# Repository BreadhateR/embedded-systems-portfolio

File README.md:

# Embedded Systems & PCB Design Portfolio

Hardware designs and experimental work from my master's thesis on the power supply of **[SiSmaK – Sensor-integrated machine element](https://www.spp2305.de/sismak/)** at TU Darmstadt. SiSmaK is a sensor-integrated M20 bolt that measures multiaxial mechanical loads using strain gauges and transmits the readings wirelessly. The thesis investigated photovoltaic harvesting, externally driven ultrasonic power transfer, and NFC power transfer as alternative supplies for the existing sensor electronics.

My work covered power-supply concepts, component selection, schematic and PCB design, analog measurement circuits, firmware adaptations, system integration, and experimental characterization. The main challenges were the approximately **13 mm PCB diameter**, limited storage capacity, and MCU startup and measurement bursts that exceed the available harvesting power. Each project README explains its circuit, design decisions, and validation scope alongside the KiCad files and existing hardware PDF.

## Projects

| Project | Focus | Documentation |
| --- | --- | --- |
| **[MCU Board](Kicad_Files/MCU_Board/)** | Separate Nordic MCU development-board design with RF, SWD and GPIO interfaces | [README](Kicad_Files/MCU_Board/README.md) · [Hardware design](Kicad_Files/MCU_Board/Hardware_Design.pdf) |
| **[Solar Harvester — Battery](Kicad_Files/Harvesting_Solar_Akku/)** | AEM10300 photovoltaic supply using the existing SiSmaK rechargeable cell | [README](Kicad_Files/Harvesting_Solar_Akku/README.md) · [Hardware design](Kicad_Files/Harvesting_Solar_Akku/Hardware_Design.pdf) |
| **[Solar Harvester — Capacitor](Kicad_Files/Harvester_Solar_Kondensator/)** | Photovoltaic supply with 150 µF storage and a storage-controlled output gate | [README](Kicad_Files/Harvester_Solar_Kondensator/README.md) · [Hardware design](Kicad_Files/Harvester_Solar_Kondensator/Hardware_Design.pdf) |
| **[Piezo Harvester — Battery](Kicad_Files/Harvester_Piezo_Akku/)** | Ultrasonic receiver supply with Greinacher rectification and AEM30300 load adjustment | [README](Kicad_Files/Harvester_Piezo_Akku/README.md) · [Hardware design](Kicad_Files/Harvester_Piezo_Akku/Hardware_Design.pdf) |
| **[Piezo Harvester — Capacitor](Kicad_Files/Harvester_Piezo_Kondensator/)** | Ultrasonic supply architecture with capacitor storage and phased measurement operation | [README](Kicad_Files/Harvester_Piezo_Kondensator/README.md) · [Hardware design](Kicad_Files/Harvester_Piezo_Kondensator/Hardware_Design.pdf) |
| **[Piezo Harvester with Measurements](Kicad_Files/Harvester_Piezo_WithMeasurements/)** | Compact rectifier-output voltage/current measurement design for frequency ranking | [README](Kicad_Files/Harvester_Piezo_WithMeasurements/README.md) · [Hardware design](Kicad_Files/Harvester_Piezo_WithMeasurements/Hardware_Design.pdf) |
| **[Piezo Harvesting & Resonance Evaluation Board](Kicad_Files/Harvester_Piezo_WithMeasurements__DevBoard/)** | Configurable harvesting and measurement platform with XIAO nRF54L15 and SiSmaK interfaces | [README](Kicad_Files/Harvester_Piezo_WithMeasurements__DevBoard/README.md) · [Hardware design](Kicad_Files/Harvester_Piezo_WithMeasurements__DevBoard/Hardware_Design.pdf) |
| **[NFC Harvester](Kicad_Files/NFC_Harvester/)** | NTAG 5 Link receiver with antenna tuning and reverse-current blocking | [README](Kicad_Files/NFC_Harvester/README.md) · [Hardware design](Kicad_Files/NFC_Harvester/Hardware_Design.pdf) |

## Repository Structure

```text
Kicad_Files/
├── MCU_Board/
├── Harvesting_Solar_Akku/
├── Harvester_Solar_Kondensator/
├── Harvester_Piezo_Akku/
├── Harvester_Piezo_Kondensator/
├── Harvester_Piezo_WithMeasurements/
├── Harvester_Piezo_WithMeasurements__DevBoard/
├── NFC_Harvester/
└── Libraries/
    ├── 3D/
    ├── Footprints/
    └── Symbols/
```

Project directories generally include:

- `*.kicad_pro`, `*.kicad_sch`, `*.kicad_pcb` — editable KiCad project, schematic, and PCB layout
- `README.md` — project-specific description
- `Hardware_Design.pdf` — exported hardware documentation
- `images/` — board renders or layout images
- `bom/` — bill-of-materials exports where available, including interactive BOMs

Shared custom symbols, footprints, and 3D models are located in [`Kicad_Files/Libraries/`](Kicad_Files/Libraries/).

## Viewing the Designs

Open a project's `.kicad_pro` file in **KiCad** to inspect its schematic and PCB layout. For a quick overview without KiCad, use the project's README, PDF documentation, and available interactive BOM (`bom/ibom.html`).

## Project Context

The existing SiSmaK sensor electronics, flexible PCB, and overall bolt concept formed the integration baseline. The harvesting modules and associated firmware/measurement work documented here extend that system; they do not represent development of the complete SiSmaK platform.

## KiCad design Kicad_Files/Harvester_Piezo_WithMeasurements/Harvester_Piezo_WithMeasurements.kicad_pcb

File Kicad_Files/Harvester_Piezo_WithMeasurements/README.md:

# SiSmaK – Piezoelectric Resonance Measurement Board

Compact harvesting and measurement PCB developed for the [SiSmaK research project](https://www.spp2305.de/sismak/) at TU Darmstadt. It investigates how frequency-search electronics can fit within the approximately 13 mm installation envelope of the sensor-integrated M20 bolt.

The board combines AEM30300 harvesting with switchable measurement paths at the **DC output of the Greinacher rectifier**. Measuring open-circuit voltage and approximate short-circuit current at different excitation frequencies supports ranking of useful ultrasonic operating points without a full load sweep at every frequency.

Development focused on the analog signal paths, MCU-controlled measurement states, and two-sided PCB integration. An FPC interface routes supply, control, and measurement signals to the existing SiSmaK electronics; a separate development board provides access for commissioning and experiments.

## PCB Design

<table>
  <tr>
    <th align="center">Front Side</th>
    <th align="center">Back Side</th>
  </tr>
  <tr>
    <td width="50%" align="center"></td>
    <td width="50%" align="center"></td>
  </tr>
</table>

## Hardware Overview

- **Energy Harvesting IC:** e-peas AEM30300 for piezoelectric energy harvesting and power management.
- **Piezoelectric Input:** External piezoelectric transducer connected through an MHF4 connector.
- **Rectification:** Greinacher voltage doubler using Schottky diodes for converting the piezoelectric AC signal into DC voltage.
- **Current Measurement:** INA190 current-sense amplifier with a 30 Ω shunt; the thesis uses 200 V/V gain.
- **Voltage Measurement:** 6.8 MΩ / 3.3 MΩ divider, approximately 1:3 reduction, with an ADC charge-buffer capacitor.
- **Measurement Control:** MOSFET-based switching circuit for controlling the measurement conditions.
- **System Interface:** FPC connection to the existing SiSmaK electronics, carrying power, measurement signals and control connections.
- **Form Factor:** Compact circular PCB designed for integration into the space-constrained SiSmaK assembly.

## Operating Principle

The circuit separates energy collection from voltage/current characterization so the changing operating state of the harvesting IC has less influence on comparisons between excitation frequencies.

### Piezoelectric Energy Harvesting

The alternating voltage generated by the piezoelectric transducer is rectified using a Greinacher voltage doubler consisting of Schottky diodes and capacitors.

The resulting DC voltage is supplied to the AEM30300 energy harvesting IC, which manages the harvested energy and provides an interface for the connected system.

### Resonance Characterization

The nRF54L15's internal ADC acquires the rectifier-output measurements, avoiding an additional external ADC on the compact module.

- **Open-Circuit Voltage (Voc):** Storage charging is disabled to reduce harvester loading. The AEM30300 remains connected; the thesis found no relevant measurement influence after its supply capacitors had charged.
- **Short-Circuit Current (Isc):** A MOSFET switches the rectifier output through the low-resistance shunt path, and the INA190 amplifies the shunt voltage for ADC acquisition.

The SiSmaK microcontroller controls the measurement circuitry through the FPC interface, switching between open-circuit voltage and short-circuit current measurements. The measured signals are transferred through the same interface for acquisition and processing.

The product **Voc × Isc** is a frequency-ranking criterion, not power delivered into a load: its two factors are measured in different states. The thesis found a close empirical relationship to maximum available power for the investigated configuration (§5.4.1). Divider/filter settling after switching limits measurement speed; amplifier output swing limits the current range.

## Hardware Design Files

The KiCad schematic and PCB design files are included in the project directory for further inspection.

[View Hardware Design Documentation (PDF)](Hardware_Design.pdf)

## Project Context

This PCB was developed as part of research and development activities associated with the [SiSmaK project](https://www.spp2305.de/sismak/) at the Institute of Production Management, Technology and Machine Tools (PTW), TU Darmstadt.

The compact layout establishes the spatial feasibility of the measurement circuit (§5.4.2). Commissioning, firmware integration into the existing SiSmaK project, and experimental frequency sweeps are reported with the development setup (§5.4.3);

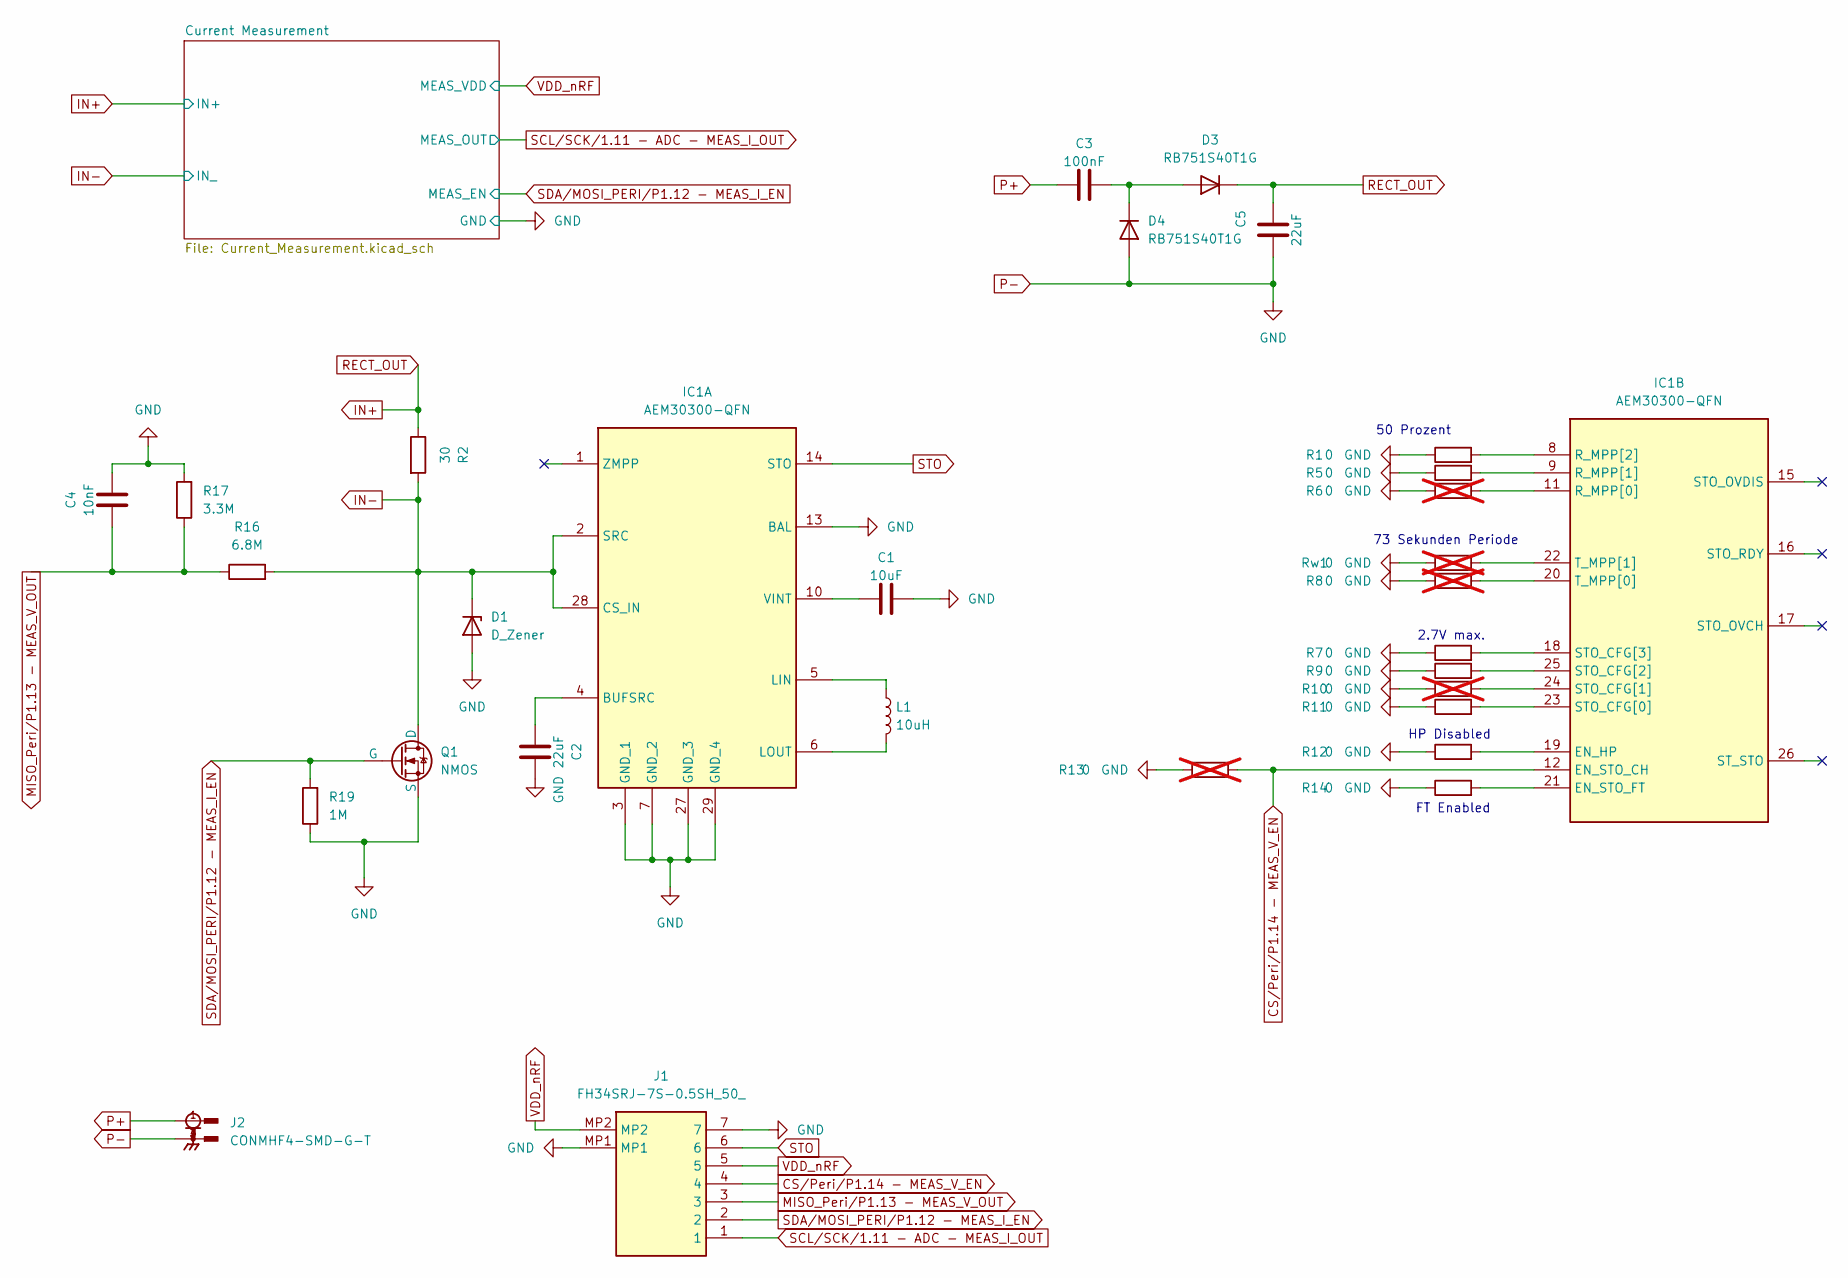
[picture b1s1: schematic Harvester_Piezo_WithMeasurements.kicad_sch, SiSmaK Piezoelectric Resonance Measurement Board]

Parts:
C1: 10uF; C_0402_1005Metric_Pad0.74x0.62mm_HandSolder; MPN GRM155R60J106ME15D
C2: 22uF; C_0603_1608Metric; MPN GRM188R61A226ME15D
C3: 100nF; 0704; MPN GRMJN65C1H104JE01J
C4: 10nF; C_0402_1005Metric_Pad0.74x0.62mm_HandSolder; MPN GRM1555CYA103GE01J
C5: 22uF; C_0603_1608Metric; MPN MLASL168BB5226MTNA01
D1: D_Zener; SODFL1608X70N; MPN MM5Z5V6T1G
D3, D4: RB751S40T1G; Diode_RB751S40T1G; MPN RB751S40T1G
IC1: AEM30300-QFN; AEM30300; Manufacturer_Part_Number AEM30300-QFN
J1: FH34SRJ-7S-0.5SH_50_; FH34SRJ7S05SH50; Manufacturer_Part_Number FH34SRJ-7S-0.5SH(50); Mouser Part Number 798-FH34SRJ7S05SH50
J2: CONMHF4-SMD-G-T; PARTREV A
L1: 10uH; DFE252010F-100M=P2; MPN DFE252010F-100M=P2
Q1: NMOS; SOT-523; MPN DMN2310UTQ-7
R1, R5, R7, R9, R11, R12, R14: 0; R_01005_0402Metric; MPN RC0201JR-130RL
R2: 30; R_0402_1005Metric_Pad0.72x0.64mm_HandSolder; MPN RT0402BRE0730RL
R6, R8, R10, R13: 0; R_01005_0402Metric; MPN RC0201JR-130RL; not fitted
R16: 6.8M; R_0402_1005Metric_Pad0.72x0.64mm_HandSolder; MPN RC0402FR-076M8L
R17: 3.3M; R_0402_1005Metric_Pad0.72x0.64mm_HandSolder; MPN CRCW04023M30FKEDC
R19: 1M; R_0402_1005Metric_Pad0.72x0.64mm_HandSolder; MPN RC0402FR-071MP
Rw1: 0; R_01005_0402Metric; MPN RC0201JR-130RL; not fitted

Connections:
CS/Peri/P1.14 - MEAS_V_EN: IC1.12 (EN_STO_CH), J1.4, R13.2
IN+: C5.2, D3.1 (K), R2.1; also elsewhere on the board
IN-: D1.1 (K), IC1.2 (SRC), IC1.28 (CS_IN), Q1.3 (D), R2.2, R16.2; also elsewhere on the board
MISO_Peri/P1.13 - MEAS_V_OUT: C4.2, J1.3, R16.1, R17.1
unnamed: C3.1, D3.2 (A), D4.1 (K)
unnamed: C2.2, IC1.4 (BUFSRC)
unnamed: IC1.5 (LIN), L1.1
unnamed: IC1.6 (LOUT), L1.2
unnamed: C1.2, IC1.10 (VINT)
unnamed: IC1.19 (EN_HP), R12.2
unnamed: IC1.21 (EN_STO_FT), R14.2
unnamed: IC1.11 (R_MPP[0]), R6.2
unnamed: IC1.9 (R_MPP[1]), R5.2
unnamed: IC1.8 (R_MPP[2]), R1.2
unnamed: IC1.23 (STO_CFG[0]), R11.2
unnamed: IC1.24 (STO_CFG[1]), R10.2
unnamed: IC1.25 (STO_CFG[2]), R9.2
unnamed: IC1.18 (STO_CFG[3]), R7.2
unnamed: IC1.20 (T_MPP[0]), R8.2
unnamed: IC1.22 (T_MPP[1]), Rw1.2
P+: C3.2, J2.1
P-: C1.1, C2.1, C4.1, C5.1, D1.2 (A), D4.2 (A), IC1.3 (GND_1), IC1.7 (GND_2), IC1.13 (BAL), IC1.27 (GND_3), IC1.29 (GND_4), J1.7, J1.MP1, J2.2, J2.3, J2.4, Q1.2 (S), R1.1, R5.1, R6.1, R7.1, R8.1, R9.1, R10.1, R11.1, R12.1, R13.1, R14.1, R17.2, R19.1, Rw1.1; also elsewhere on the board
SCL/SCK/1.11 - ADC - MEAS_I_OUT: J1.1; also elsewhere on the board
SDA/MOSI_PERI/P1.12 - MEAS_I_EN: J1.2, Q1.1 (G), R19.2; also elsewhere on the board
STO: IC1.14 (STO), J1.6
VDD_nRF: J1.5, J1.MP2; also elsewhere on the board

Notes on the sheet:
FT Enabled
50 Prozent
73 Sekunden Periode
HP Disabled
2.7V max.

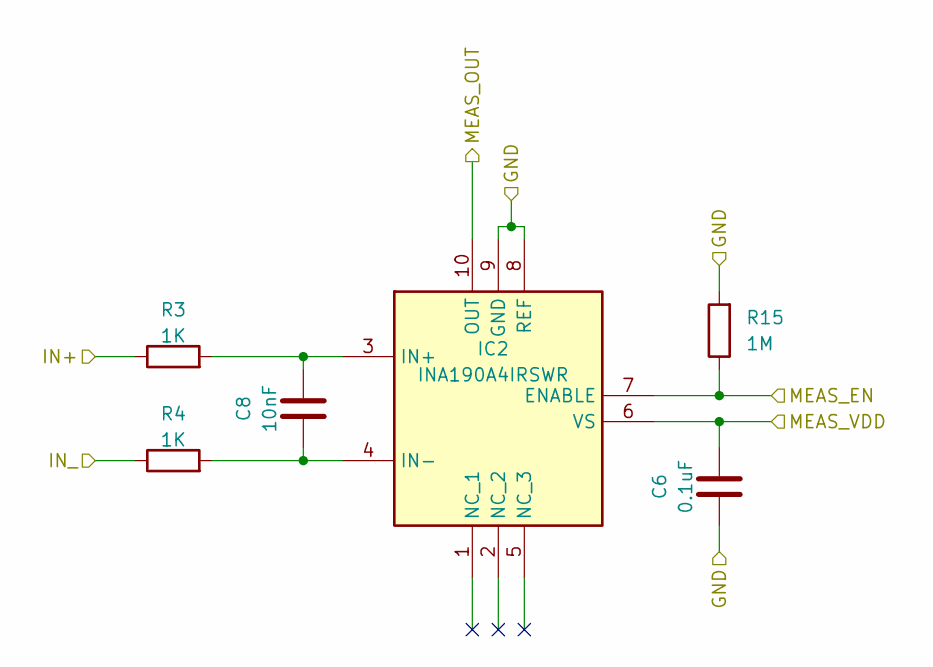
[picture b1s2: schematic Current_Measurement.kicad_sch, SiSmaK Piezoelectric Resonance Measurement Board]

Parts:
C6: 0.1uF; C_0402_1005Metric_Pad0.74x0.62mm_HandSolder; MPN CGA2B2X5R1C104M050BA
C8: 10nF; C_0402_1005Metric_Pad0.74x0.62mm_HandSolder; MPN GRM1555CYA103GE01J
IC2: INA190A4IRSWR; QFN40P140X180X55-10N; Manufacturer_Part_Number INA190A4IRSWR; Mouser Part Number 595-INA190A4IRSWR
R3, R4: 1K; R_0402_1005Metric_Pad0.72x0.64mm_HandSolder; MPN RNCF0402BTE1K00
R15: 1M; R_0402_1005Metric_Pad0.72x0.64mm_HandSolder; MPN RC0402FR-071MP

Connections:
IN+: R3.1; also elsewhere on the board
IN-: R4.1; also elsewhere on the board
unnamed: C8.1, IC2.3 (IN+), R3.2
unnamed: C8.2, IC2.4 (IN-), R4.2
P-: C6.2, IC2.8 (REF), IC2.9 (GND), R15.2; also elsewhere on the board
SCL/SCK/1.11 - ADC - MEAS_I_OUT: IC2.10 (OUT); also elsewhere on the board
SDA/MOSI_PERI/P1.12 - MEAS_I_EN: IC2.7 (ENABLE), R15.1; also elsewhere on the board
VDD_nRF: C6.1, IC2.6 (VS); also elsewhere on the board

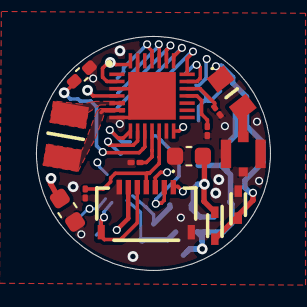
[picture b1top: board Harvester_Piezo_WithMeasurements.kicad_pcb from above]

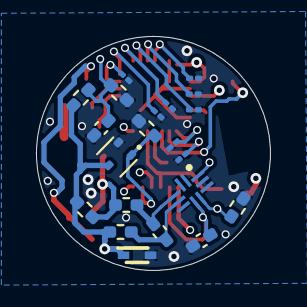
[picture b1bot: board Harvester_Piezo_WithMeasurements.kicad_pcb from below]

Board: 4 copper layers, 13.0 x 13.0 mm, 35 parts (21 on the bottom side), 28 nets.

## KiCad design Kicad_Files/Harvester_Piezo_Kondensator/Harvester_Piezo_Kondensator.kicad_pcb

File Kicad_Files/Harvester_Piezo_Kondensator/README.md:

# SiSmaK Piezoelectric Energy Harvesting Module – Capacitor

Capacitor-buffered ultrasonic supply design for the existing **[SiSmaK](https://www.spp2305.de/sismak/)** sensor-integrated M20 bolt. The circular PCB connects through an **FPC interface**, stores energy from an external piezoelectric receiver, and delays load connection until sufficient storage voltage is available.

Development combined rectification and storage circuitry, a controlled output path, compact PCB layout, and firmware adaptations that divide sensor acquisition into tasks separated by recharge pauses.

## Hardware Features

- **Energy Harvesting IC:** AEM30300 in the thesis architecture; supplied IC1 fields are inconsistent (see Project Status)
- **Energy Source:** External piezoelectric transducer
- **Piezoelectric Input:** External transducer connection via MHF4 connector
- **Rectification:** Greinacher voltage-doubler circuit using Schottky diodes
- **Energy Storage:** 150 µF nominal capacitor
- **Power Management:** Inductive DC-DC conversion and storage-voltage monitoring
- **Operating Concept:** Harvest–Store–Partial–Use, retaining RAM during sleep/recharge pauses
- **System Interface:** FPC connection to the existing SiSmaK electronics
- **Form Factor:** Compact circular PCB for space-constrained integration

### Piezoelectric Energy Harvesting

The piezoelectric receiver generates AC under externally driven ultrasonic excitation. A Greinacher voltage doubler rectifies the signal, and the harvesting stage transfers energy to the capacitor.

An ST_STO-controlled PMOS/NMOS output gate keeps the load disconnected during initial charging. Once enabled, the MCU boots and performs individual strain-gauge measurements, entering sleep between tasks while the capacitor recharges. Maintaining the MCU supply preserves RAM and avoids another energy-intensive boot.

### SiSmaK Integration

The module was designed as an add-on to the existing SiSmaK electronics rather than a standalone development board. The piezoelectric transducer connects through an MHF4 connector, while the FPC interface provides the electrical connection to the sensor-integrating bolt system. The FPC connector is visible on the back side of the PCB.

## PCB Design

The approximately 13 mm, four-layer PCB was designed in **KiCad 9**. Two-sided placement accommodates the rectifier, storage, and output-control circuitry; the FPC connector is on the reverse side.

### PCB View

<table>
  <tr>
    <th align="center">Front Side</th>
    <th align="center">Back Side</th>
  </tr>
  <tr>
    <td width="50%" align="center"></td>
    <td width="50%" align="center"></td>
  </tr>
</table>

## Hardware Design Documentation

The KiCad schematic and PCB design files are included for further inspection.

[View Hardware Design Documentation (PDF)](Hardware_Design.pdf)

## Design Files

| File | Description |
|---|---|
| `Harvester_Piezo_Kondensator.kicad_pro` | KiCad project |
| `Harvester_Piezo_Kondensator.kicad_sch` | Electrical schematic |
| `Harvester_Piezo_Kondensator.kicad_pcb` | PCB layout |
| `images/Harvester_Piezo_Kondensator.png` | Front-side 3D rendering |
| `images/Harvester_Piezo_Kondensator_hinten.png` | Back-side 3D rendering |
| `Hardware_Design.pdf` | Schematic and PCB documentation |

## Project Status

The thesis demonstrates phased operation with **150 µF storage** (§5.3.2): charging to about 3.3 V followed by successful MCU boot, with capacitor voltage falling to about 1.7 V. PPK2 recordings, GPIO timing markers, and oscilloscope measurements linked individual tasks to energy use and storage-voltage changes. Reported boot energy was about **0.58 mJ over 24.5 ms**; individual strain-gauge channels required about **0.30 mJ over 14 ms**.

---

**Author:** Alexander Richter  
**Institution:** TU Darmstadt  
**Related project:** [SiSmaK – Project Website](https://www.spp2305.de/sismak/)

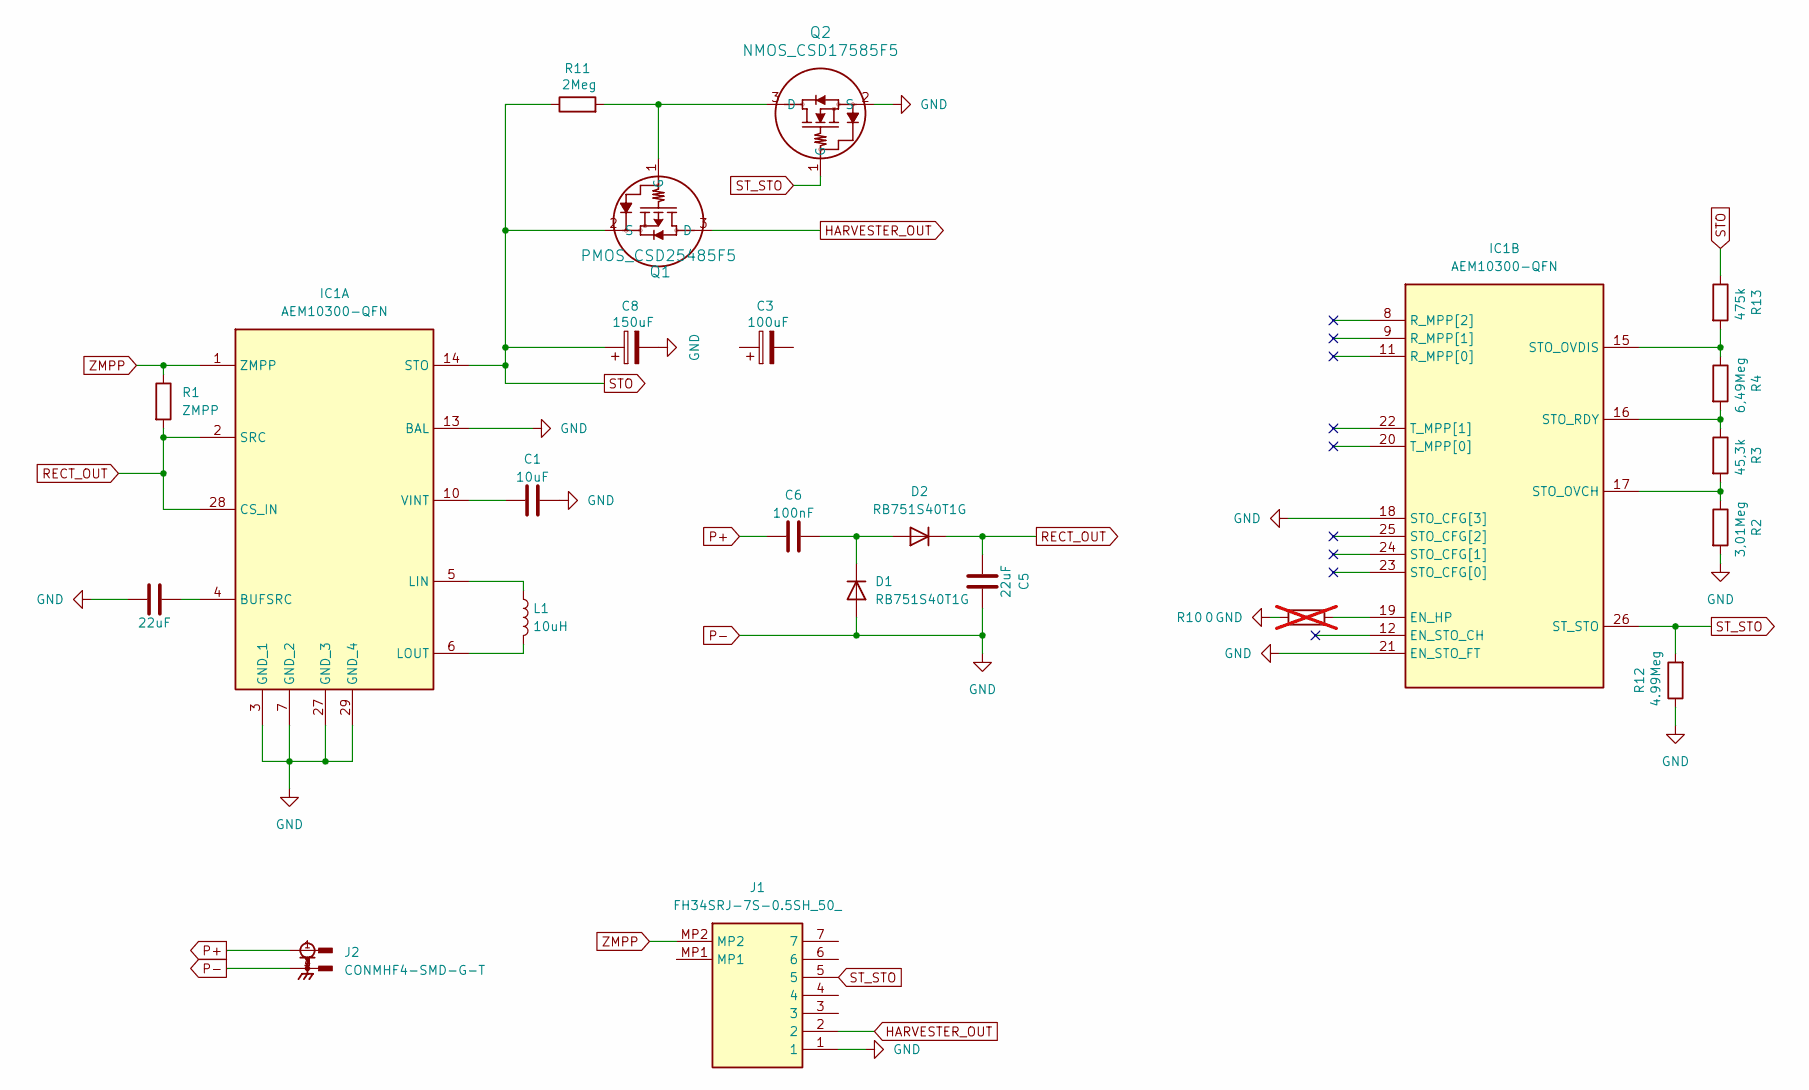
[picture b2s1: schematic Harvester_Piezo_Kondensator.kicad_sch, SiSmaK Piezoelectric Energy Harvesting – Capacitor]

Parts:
C1: 10uF; C_0402_1005Metric_Pad0.74x0.62mm_HandSolder; MPN GRM155R60J106ME15D
C2: 22uF; C_0603_1608Metric; MPN GRM188R61A226ME15D
C3: 100uF; TCTOBL1A107M8R-ZS1; MPN TCTOBL1A107M8R-ZS1
C5: 22uF; C_0603_1608Metric; MPN MLASL168BB5226MTNA01
C6: 100nF; 0704; MPN GRMJN65C1H104JE01J
C8: 150uF; T490B; MPN T490B157M010ATE500
D1, D2: RB751S40T1G; Diode_RB751S40T1G; MPN RB751S40T1G
IC1: AEM10300-QFN; AEM30300; Manufacturer_Part_Number AEM10300-QFN
J1: FH34SRJ-7S-0.5SH_50_; FH34SRJ7S05SH50; Manufacturer_Part_Number FH34SRJ-7S-0.5SH(50); Mouser Part Number 798-FH34SRJ7S05SH50
J2: CONMHF4-SMD-G-T; PARTREV A
L1: 10uH; DFE252010F-100M=P2; MPN DFE252010F-100M=P2
Q1: PMOS_CSD25485F5; MPN CSD25485F5
Q2: NMOS_CSD17585F5; MPN CSD17585F5
R1: ZMPP; R_0402_1005Metric_Pad0.72x0.64mm_HandSolder
R2: 3,01Meg; R_0402_1005Metric_Pad0.72x0.64mm_HandSolder; MPN CRCW04023M01FKED
R3: 45,3k; R_0402_1005Metric_Pad0.72x0.64mm_HandSolder; MPN 560112110243
R4: 6,49Meg; R_0402_1005Metric_Pad0.72x0.64mm_HandSolder; MPN RC0402FR-076M49L
R10: 0; C_0201_0603Metric_Pad0.64x0.40mm_HandSolder; not fitted
R11: 2Meg; R_0402_1005Metric_Pad0.72x0.64mm_HandSolder; MPN CRCW04022M00FKEDC
R12: 4.99Meg; R_0402_1005Metric_Pad0.72x0.64mm_HandSolder; MPN CRCW04024M99FKED
R13: 475k; R_0402_1005Metric_Pad0.72x0.64mm_HandSolder; MPN RC0402FR-07475KL

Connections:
HARVESTER_OUT: J1.2, Q1.3 (D)
unnamed: C6.1, D1.1 (K), D2.2 (A)
unnamed: C2.2, IC1.4 (BUFSRC)
unnamed: IC1.5 (LIN), L1.1
unnamed: IC1.6 (LOUT), L1.2
unnamed: C1.2, IC1.10 (VINT)
unnamed: IC1.19 (EN_HP), R10.2
unnamed: IC1.17 (STO_OVCH), R2.1, R3.2
unnamed: IC1.15 (STO_OVDIS), R4.1, R13.2
unnamed: IC1.16 (STO_RDY), R3.1, R4.2
unnamed: Q1.1 (G), Q2.3 (D), R11.2
P+: C6.2, J2.1
P-: C1.1, C2.1, C5.1, C8.2, D1.2 (A), IC1.3 (GND_1), IC1.7 (GND_2), IC1.13 (BAL), IC1.18 (STO_CFG[3]), IC1.21 (EN_STO_FT), IC1.27 (GND_3), IC1.29 (GND_4), J1.1, J2.2, J2.3, J2.4, Q2.2 (S), R2.2, R10.1, R12.1
RECT_OUT: C5.2, D2.1 (K), IC1.2 (SRC), IC1.28 (CS_IN), R1.2
STO: C8.1, IC1.14 (STO), Q1.2 (S), R11.1, R13.1
ST_STO: IC1.26 (ST_STO), J1.5, Q2.1 (G), R12.2
ZMPP: IC1.1 (ZMPP), J1.MP2, R1.1

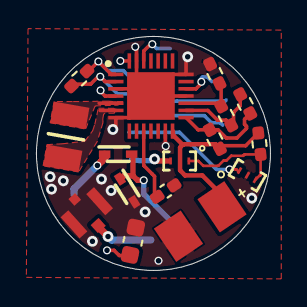
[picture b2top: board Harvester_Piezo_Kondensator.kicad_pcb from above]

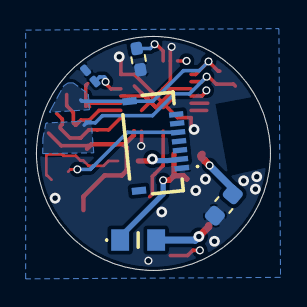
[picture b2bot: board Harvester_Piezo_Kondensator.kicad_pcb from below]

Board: 4 copper layers, 13.0 x 13.0 mm, 21 parts (5 on the bottom side), 17 nets.

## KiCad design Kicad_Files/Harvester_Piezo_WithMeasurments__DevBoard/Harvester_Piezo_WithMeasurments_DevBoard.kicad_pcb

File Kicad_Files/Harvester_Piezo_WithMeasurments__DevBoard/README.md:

# Piezoelectric Energy Harvesting & Resonance Evaluation Board

Development and evaluation platform for piezoelectric energy harvesting and resonance-frequency search in the **[SiSmaK](https://www.spp2305.de/sismak/)** project at TU Darmstadt.

## Overview

This development board combines a piezoelectric energy-harvesting circuit with switchable voltage and current measurement paths. It supports characterization of a piezoelectric transducer during a frequency sweep, evaluation of the AEM30300 harvesting circuit, and experiments with different energy-storage configurations.

The board can be used with the **SiSmaK electronics** or with a **Seeed Studio XIAO nRF54L15** development board. The connected microcontroller controls the measurement modes and acquires the measurement signals.

## Hardware Features

- **Energy harvesting IC:** e-peas AEM30300 for piezoelectric energy harvesting, with configurable MPP and storage settings.
- **Piezoelectric input:** External transducer connection via MHF4 connector; additional connection and test points are provided on the development board.
- **Rectification:** Greinacher voltage-doubler rectifier using RB751S40 Schottky diodes, with a rectified output available for the harvester.
- **Energy storage:** Selectable battery or capacitor operation, with a storage connector and configuration jumpers.
- **Open-circuit voltage (Voc):** A switchable high-impedance voltage-measurement path. The AEM30300 input can be disconnected during measurement, and the piezoelectric voltage is sensed through a resistor divider.
- **Short-circuit current (Isc):** A MOSFET-controlled low-resistance measurement path using a shunt resistor and an INA190 current-sense amplifier.
- **Measurement control:** Microcontroller-controlled switching between operating and measurement conditions; voltage and current signals are routed to the MCU for acquisition.
- **MCU compatibility:** Connections for both the SiSmaK electronics and a Seeed Studio XIAO nRF54L15 development board.
- **Evaluation interfaces:** Jumpers, headers, test points and configuration options for AEM30300 settings, storage selection, and power-path experiments.

## Resonance Search

During a frequency sweep, the microcontroller can switch the board into the required measurement configuration and acquire the piezoelectric transducer's open-circuit voltage or short-circuit current. The resulting frequency-dependent measurements can be used to identify resonance-related peaks and evaluate suitable excitation frequencies for energy harvesting.

For **Voc measurement**, the harvesting input is isolated to reduce transducer loading, and the voltage is acquired via the high-impedance divider. For **Isc measurement**, the MOSFET enables the low-resistance shunt path and the INA190 provides a measurable output signal.

## Energy Storage and Operation

The AEM30300 harvests energy from the rectified piezoelectric signal. The board provides configuration options for **battery-backed** and **capacitor-based** operation, enabling comparison of continuous energy-buffered use and charge/discharge operating cycles. Jumpers and switches allow the harvesting, storage and output paths to be evaluated independently.

## Hardware Design Documentation

The KiCad schematic and PCB design files are included for further inspection.

[View Hardware Design Documentation (PDF)](Hardware_Design.pdf)

## Project

**[SiSmaK – Sensor-integrated machine element](https://www.spp2305.de/sismak/)**  
TU Darmstadt

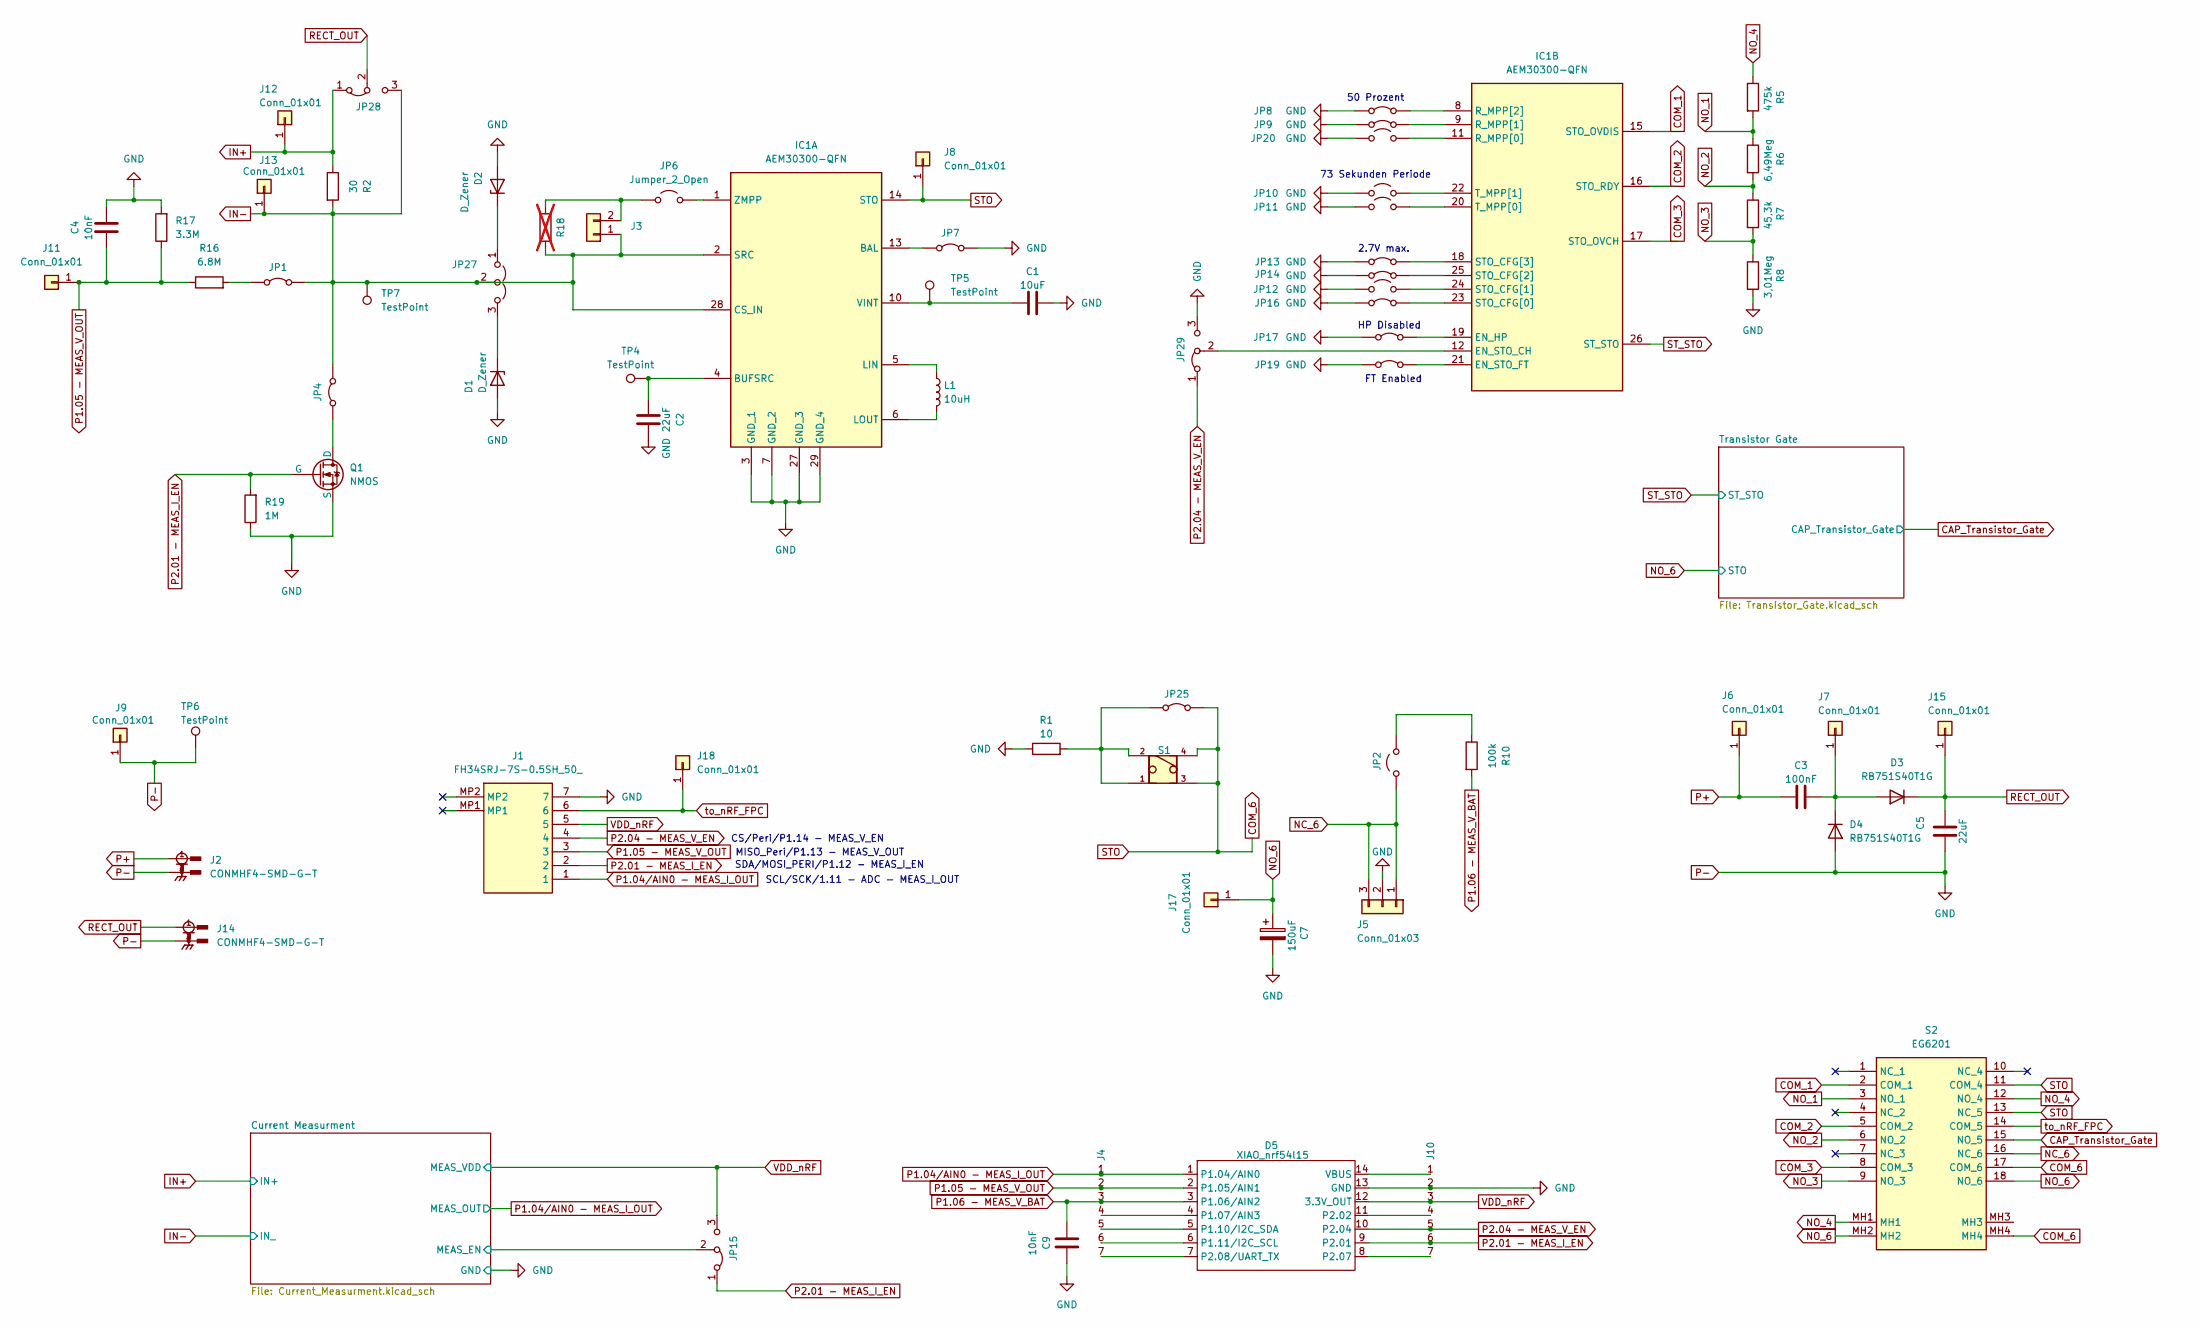
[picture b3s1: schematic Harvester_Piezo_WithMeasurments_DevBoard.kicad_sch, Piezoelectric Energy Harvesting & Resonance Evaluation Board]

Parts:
C1: 10uF; C_0402_1005Metric_Pad0.74x0.62mm_HandSolder; MPN GRM155R60J106ME15D
C2: 22uF; C_0603_1608Metric; MPN GRM188R61A226ME15D
C3: 100nF; 0704; MPN GRMJN65C1H104JE01J
C4, C9: 10nF; C_0402_1005Metric_Pad0.74x0.62mm_HandSolder; MPN GRM1555CYA103GE01J
C5: 22uF; C_0603_1608Metric; MPN MLASL168BB5226MTNA01
C7: 150uF; T490B; MPN T490B157M010ATE500
D1: D_Zener; SODFL1608X70N; MPN MM5Z5V6T1G
D2: D_Zener; SODFL1608X70N; MPN MM5Z5V1T1G
D3, D4: RB751S40T1G; Diode_RB751S40T1G; MPN RB751S40T1G
D5: XIAO_nrf54l15; XIAO-nRF54l15-Steckleisten_Female; MPN CES-114-02-T-S
IC1: AEM30300-QFN; AEM30300; Manufacturer_Part_Number AEM30300-QFN
J1: FH34SRJ-7S-0.5SH_50_; FH34SRJ7S05SH50; Manufacturer_Part_Number FH34SRJ-7S-0.5SH(50); Mouser Part Number 798-FH34SRJ7S05SH50
J2, J14: CONMHF4-SMD-G-T; PARTREV A
J3: Conn_01x02; CONN_1729128_PXC; MPN 1729128
J4: Conn_01x07_Pin; PinHeader_1x07_P2.54mm_Vertical; MPN CES-114-02-T-S
J5: Conn_01x03; PinHeader_1x03_P2.54mm_Horizontal; MPN PH1RB-03-UA
J6, J7, J8, J9, J11, J12, J13, J15, J17, J18: Conn_01x01; PinHeader_1x01_P2.54mm_Vertical; MPN TSW-101-07-G-S
J10: Conn_01x07_Pin; PinHeader_1x07_P2.54mm_Vertical; MPN` CES-114-02-T-S
JP1, JP4, JP7, JP8, JP9, JP13, JP14, JP16, JP17, JP19: Jumper_2_Bridged; Header_1x2_Jumper; MPN SSK01-MPH-254-A2
JP2: Jumper_2_Open; Header_1x2_Jumper; MPN SSK01-MPH-254-A2
JP6, JP10, JP11, JP12, JP20: Jumper_2_Open; PinHeader_1x02_P2.54mm_Vertical; MPN SSK01-MPH-254-A2
JP15, JP28, JP29: Jumper_3_Bridged12; PinHeader_1x03_P2.54mm_Vertical; MPN 77311-401-03LF
JP25: Jumper_2_Bridged; PinHeader_1x02_P2.54mm_Vertical; MPN SSK01-MPH-254-A2
JP27: Jumper_3_Open; PinHeader_1x03_P2.54mm_Vertical; MPN 77311-401-03LF
L1: 10uH; DFE252010F-100M=P2; MPN DFE252010F-100M=P2
Q1: NMOS; SOT-523; MPN DMN2310UTQ-7
R1: 10; R_1206_3216Metric_Pad1.30x1.75mm_HandSolder; MPN CSRT1206FT10R0
R2: 30; R_0402_1005Metric_Pad0.72x0.64mm_HandSolder; MPN RT0402BRE0730RL
R5: 475k; R_0402_1005Metric_Pad0.72x0.64mm_HandSolder; MPN RC0402FR-07475KL
R6: 6,49Meg; R_0402_1005Metric_Pad0.72x0.64mm_HandSolder; MPN RC0402FR-076M49L
R7: 45,3k; R_0402_1005Metric_Pad0.72x0.64mm_HandSolder; MPN 560112110243
R8: 3,01Meg; R_0402_1005Metric_Pad0.72x0.64mm_HandSolder; MPN CRCW04023M01FKED
R10: 100k; R_0805_2012Metric_Pad1.20x1.40mm_HandSolder; MPN RK73B2ATTE104J
R16: 6.8M; R_0402_1005Metric_Pad0.72x0.64mm_HandSolder; MPN RC0402FR-076M8L
R17: 3.3M; R_0402_1005Metric_Pad0.72x0.64mm_HandSolder; MPN CRCW04023M30FKEDC
R18: R_0603_1608Metric_Pad0.98x0.95mm_HandSolder; not fitted
R19: 1M; R_0402_1005Metric_Pad0.72x0.64mm_HandSolder; MPN RC0402FR-071MP
S1: Button_Entladen; SW_TS02-66-43-BK-160-LCR-D; PARTREV 1.0
S2: EG6201; Manufacturer_Part_Number EG6201; Mouser Part Number 612-EG6201
TP4, TP5, TP6, TP7: TestPoint; TestPoint_Pad_2.0x2.0mm

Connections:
/Current Measurment/MEAS_EN: JP15.2 (C); also elsewhere on the board
CAP_Transistor_Gate: S2.15 (NO_5); also elsewhere on the board
COM_1: IC1.15 (STO_OVDIS), S2.2 (COM_1)
COM_2: IC1.16 (STO_RDY), S2.5 (COM_2)
COM_3: IC1.17 (STO_OVCH), S2.8 (COM_3)
COM_6: IC1.14 (STO), J8.1, JP25.2 (B), S1.3, S1.4, S2.11 (COM_4), S2.13 (NC_5), S2.17 (COM_6), S2.MH4
IN+: J12.1, JP28.1 (A), R2.1; also elsewhere on the board
IN-: IC1.2 (SRC), IC1.28 (CS_IN), J3.1, J13.1, JP1.2 (B), JP4.2 (B), JP27.2 (C), JP28.3 (B), R2.2, R18.2, TP7.1; also elsewhere on the board
NC_6: J5.1, J5.3, JP2.1 (A), S2.16 (NC_6)
NO_1: R5.2, R6.1, S2.3 (NO_1)
NO_2: R6.2, R7.1, S2.6 (NO_2)
NO_3: R7.2, R8.1, S2.9 (NO_3)
NO_4: R5.1, S2.12 (NO_4), S2.MH1
NO_6: C7.1, J17.1, S2.18 (NO_6), S2.MH2; also elsewhere on the board
unnamed: D1.1 (K), JP27.3 (B)
unnamed: D2.1 (K), JP27.1 (A)
unnamed: C3.1, D3.2 (A), D4.1 (K), J7.1
unnamed: D5.4 (P1.07/AIN3), J4.4
unnamed: D5.5 (P1.10/I2C_SDA), J4.5
unnamed: D5.6 (P1.11/I2C_SCL), J4.6
unnamed: D5.11 (P2.02), J10.4
unnamed: D5.8 (P2.07), J10.7
unnamed: D5.7 (P2.08/UART_TX), J4.7
unnamed: D5.14 (VBUS), J10.1
unnamed: IC1.13 (BAL), JP7.1 (A)
unnamed: C2.2, IC1.4 (BUFSRC), TP4.1
unnamed: IC1.5 (LIN), L1.1
unnamed: IC1.6 (LOUT), L1.2
unnamed: C1.2, IC1.10 (VINT), TP5.1
unnamed: IC1.1 (ZMPP), JP6.2 (B)
unnamed: IC1.19 (EN_HP), JP17.2 (B)
unnamed: IC1.12 (EN_STO_CH), JP29.2 (C)
unnamed: IC1.21 (EN_STO_FT), JP19.2 (B)
unnamed: IC1.11 (R_MPP[0]), JP20.2 (B)
unnamed: IC1.9 (R_MPP[1]), JP9.2 (B)
unnamed: IC1.8 (R_MPP[2]), JP8.2 (B)
unnamed: IC1.23 (STO_CFG[0]), JP16.2 (B)
unnamed: IC1.24 (STO_CFG[1]), JP12.2 (B)
unnamed: IC1.25 (STO_CFG[2]), JP14.2 (B)
unnamed: IC1.18 (STO_CFG[3]), JP13.2 (B)
unnamed: IC1.20 (T_MPP[0]), JP11.2 (B)
unnamed: IC1.22 (T_MPP[1]), JP10.2 (B)
unnamed: J3.2, JP6.1 (A), R18.1
unnamed: JP1.1 (A), R16.2
unnamed: JP2.2 (B), R10.1
unnamed: JP4.1 (A), Q1.3 (D)
unnamed: JP25.1 (A), R1.2, S1.1, S1.2
P1.04/AIN0 - MEAS_I_OUT: D5.1 (P1.04/AIN0), J1.1, J4.1; also elsewhere on the board
P1.05 - MEAS_V_OUT: C4.2, D5.2 (P1.05/AIN1), J1.3, J4.2, J11.1, R16.1, R17.1
P1.06 - MEAS_V_BAT: C9.2, D5.3 (P1.06/AIN2), J4.3, R10.2
P2.01 - MEAS_I_EN: D5.9 (P2.01), J1.2, J10.6, JP15.1 (A), Q1.1 (G), R19.2
P2.04 - MEAS_V_EN: D5.10 (P2.04), J1.4, J10.5, JP29.1 (A)
P+: C3.2, J2.1, J6.1
P-: C1.1, C2.1, C4.1, C5.1, C7.2, C9.1, D1.2 (A), D2.2 (A), D4.2 (A), D5.13 (GND), IC1.3 (GND_1), IC1.7 (GND_2), IC1.27 (GND_3), IC1.29 (GND_4), J1.7, J2.2, J2.3, J2.4, J5.2, J9.1, J10.2, J14.2, J14.3, J14.4, JP7.2 (B), JP8.1 (A), JP9.1 (A), JP10.1 (A), JP11.1 (A), JP12.1 (A), JP13.1 (A), JP14.1 (A), JP16.1 (A), JP17.1 (A), JP19.1 (A), JP20.1 (A), JP29.3 (B), Q1.2 (S), R1.1, R8.2, R17.2, R19.1, TP6.1; also elsewhere on the board
RECT_OUT: C5.2, D3.1 (K), J14.1, J15.1, JP28.2 (C)
ST_STO: IC1.26 (ST_STO); also elsewhere on the board
VDD_nRF: D5.12 (3.3V_OUT), J1.5, J10.3, JP15.3 (B); also elsewhere on the board
to_nRF_FPC: J1.6, J18.1, S2.14 (COM_5)

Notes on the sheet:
CS/Peri/P1.14 - MEAS_V_EN
SCL/SCK/1.11 - ADC - MEAS_I_OUT
FT Enabled
50 Prozent
MISO_Peri/P1.13 - MEAS_V_OUT
73 Sekunden Periode
SDA/MOSI_PERI/P1.12 - MEAS_I_EN
HP Disabled
2.7V max.

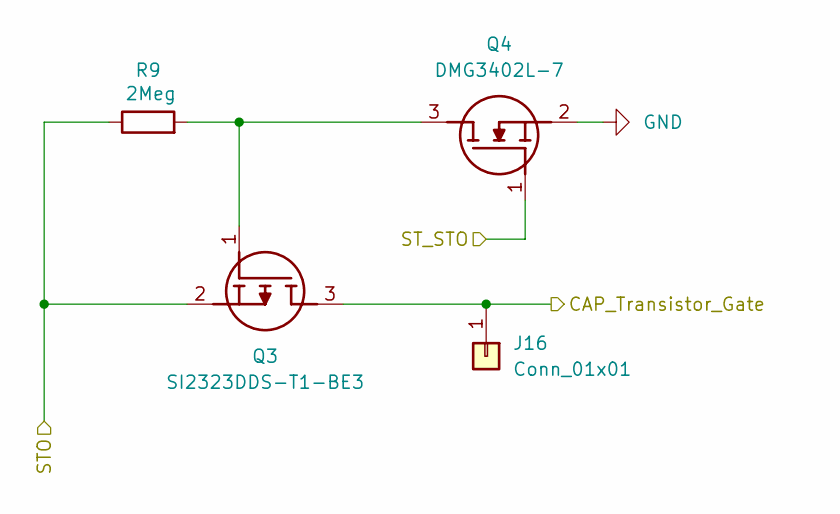
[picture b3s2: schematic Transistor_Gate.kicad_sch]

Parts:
J16: Conn_01x01; PinHeader_1x01_P2.54mm_Vertical; MPN TSW-101-07-G-S
Q3: SI2323DDS-T1-BE3; SOT95P237X112-3N; Manufacturer_Part_Number SI2323DDS-T1-BE3; Mouser Part Number 78-SI2323DDS-T1-BE3
Q4: DMG3402L-7; SOT96P240X115-3N; Manufacturer_Part_Number DMG3402L-7; Mouser Part Number 621-DMG3402L-7
R9: 2Meg; R_0402_1005Metric_Pad0.72x0.64mm_HandSolder; MPN CRCW04022M00FKEDC

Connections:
CAP_Transistor_Gate: J16.1, Q3.3 (D); also elsewhere on the board
NO_6: Q3.2 (S), R9.1; also elsewhere on the board
unnamed: Q3.1 (G), Q4.3 (D), R9.2
P-: Q4.2 (S); also elsewhere on the board
ST_STO: Q4.1 (G); also elsewhere on the board

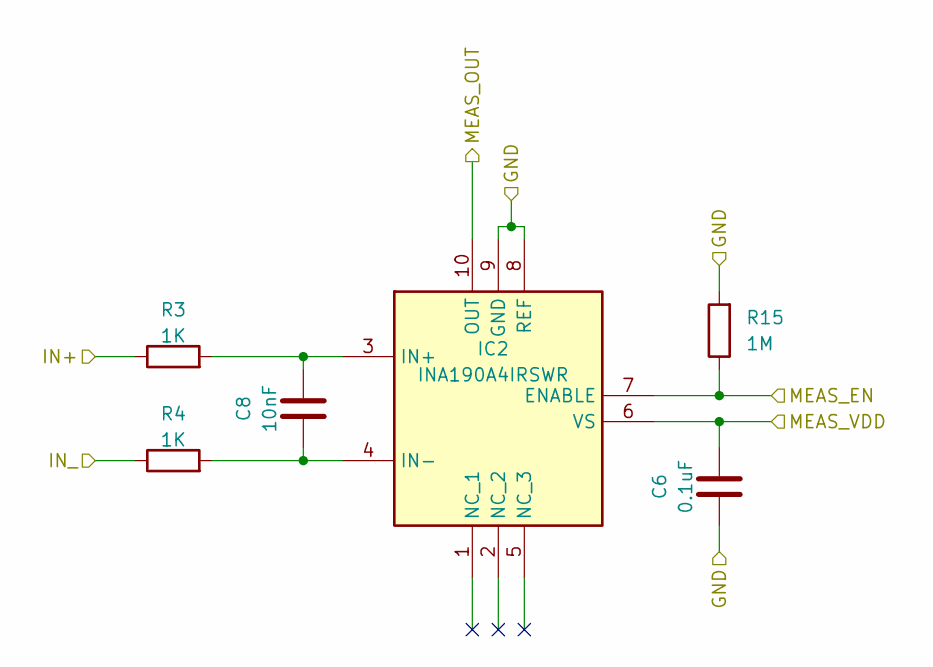
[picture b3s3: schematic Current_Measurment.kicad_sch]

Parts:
C6: 0.1uF; C_0402_1005Metric_Pad0.74x0.62mm_HandSolder; MPN CGA2B2X5R1C104M050BA
C8: 10nF; C_0402_1005Metric_Pad0.74x0.62mm_HandSolder; MPN GRM1555CYA103GE01J
IC2: INA190A4IRSWR; QFN40P140X180X55-10N; Manufacturer_Part_Number INA190A4IRSWR; Mouser Part Number 595-INA190A4IRSWR
R3, R4: 1K; R_0402_1005Metric_Pad0.72x0.64mm_HandSolder; MPN RNCF0402BTE1K00
R15: 1M; R_0402_1005Metric_Pad0.72x0.64mm_HandSolder; MPN RC0402FR-071MP

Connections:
/Current Measurment/MEAS_EN: IC2.7 (ENABLE), R15.1; also elsewhere on the board
IN+: R3.1; also elsewhere on the board
IN-: R4.1; also elsewhere on the board
unnamed: C8.1, IC2.3 (IN+), R3.2
unnamed: C8.2, IC2.4 (IN-), R4.2
P1.04/AIN0 - MEAS_I_OUT: IC2.10 (OUT); also elsewhere on the board
P-: C6.2, IC2.8 (REF), IC2.9 (GND), R15.2; also elsewhere on the board
VDD_nRF: C6.1, IC2.6 (VS); also elsewhere on the board
